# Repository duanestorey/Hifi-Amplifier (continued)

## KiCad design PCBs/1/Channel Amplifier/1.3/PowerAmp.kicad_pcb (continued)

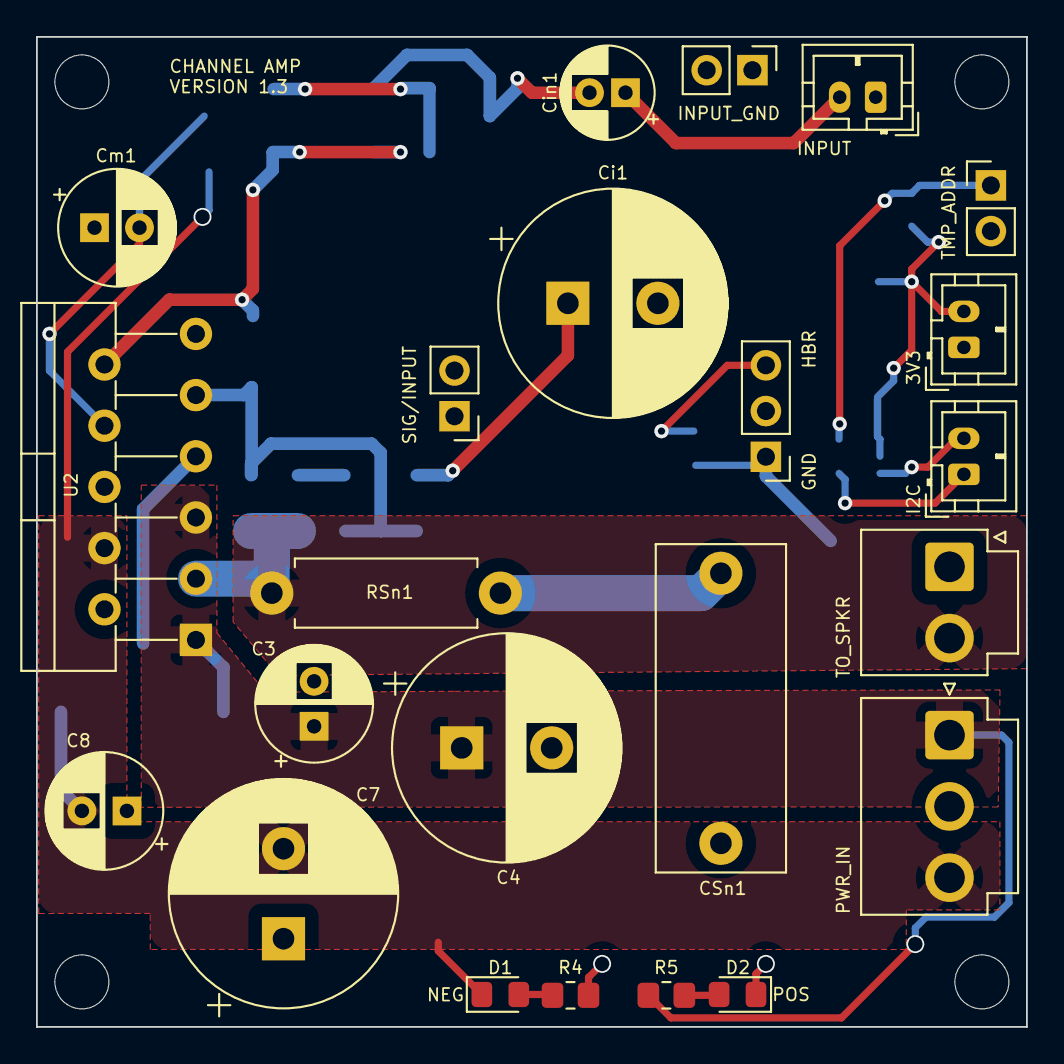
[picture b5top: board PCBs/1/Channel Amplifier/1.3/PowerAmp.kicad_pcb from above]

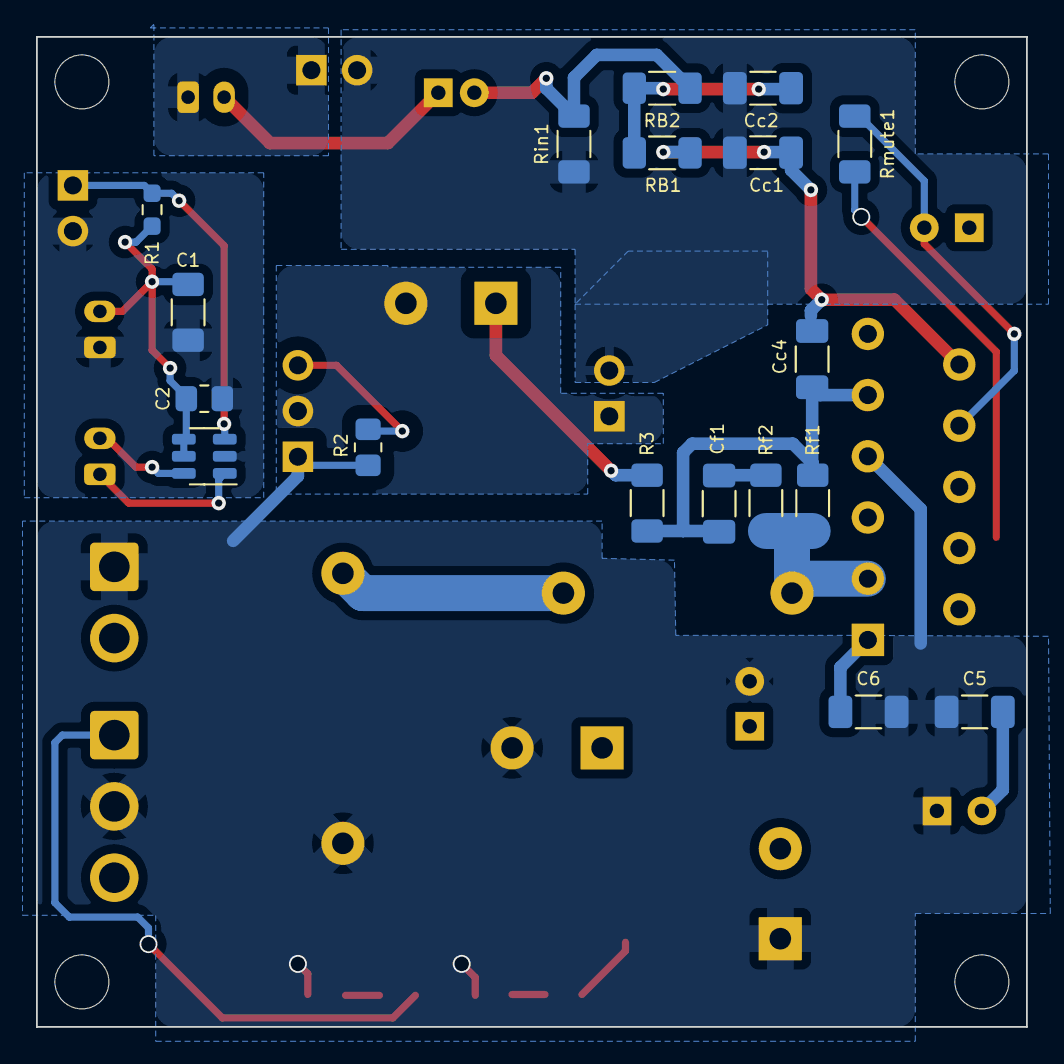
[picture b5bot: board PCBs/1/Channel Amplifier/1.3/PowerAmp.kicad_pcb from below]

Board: 2 copper layers, 55.0 x 55.0 mm, 45 parts (18 on the bottom side), 24 nets.

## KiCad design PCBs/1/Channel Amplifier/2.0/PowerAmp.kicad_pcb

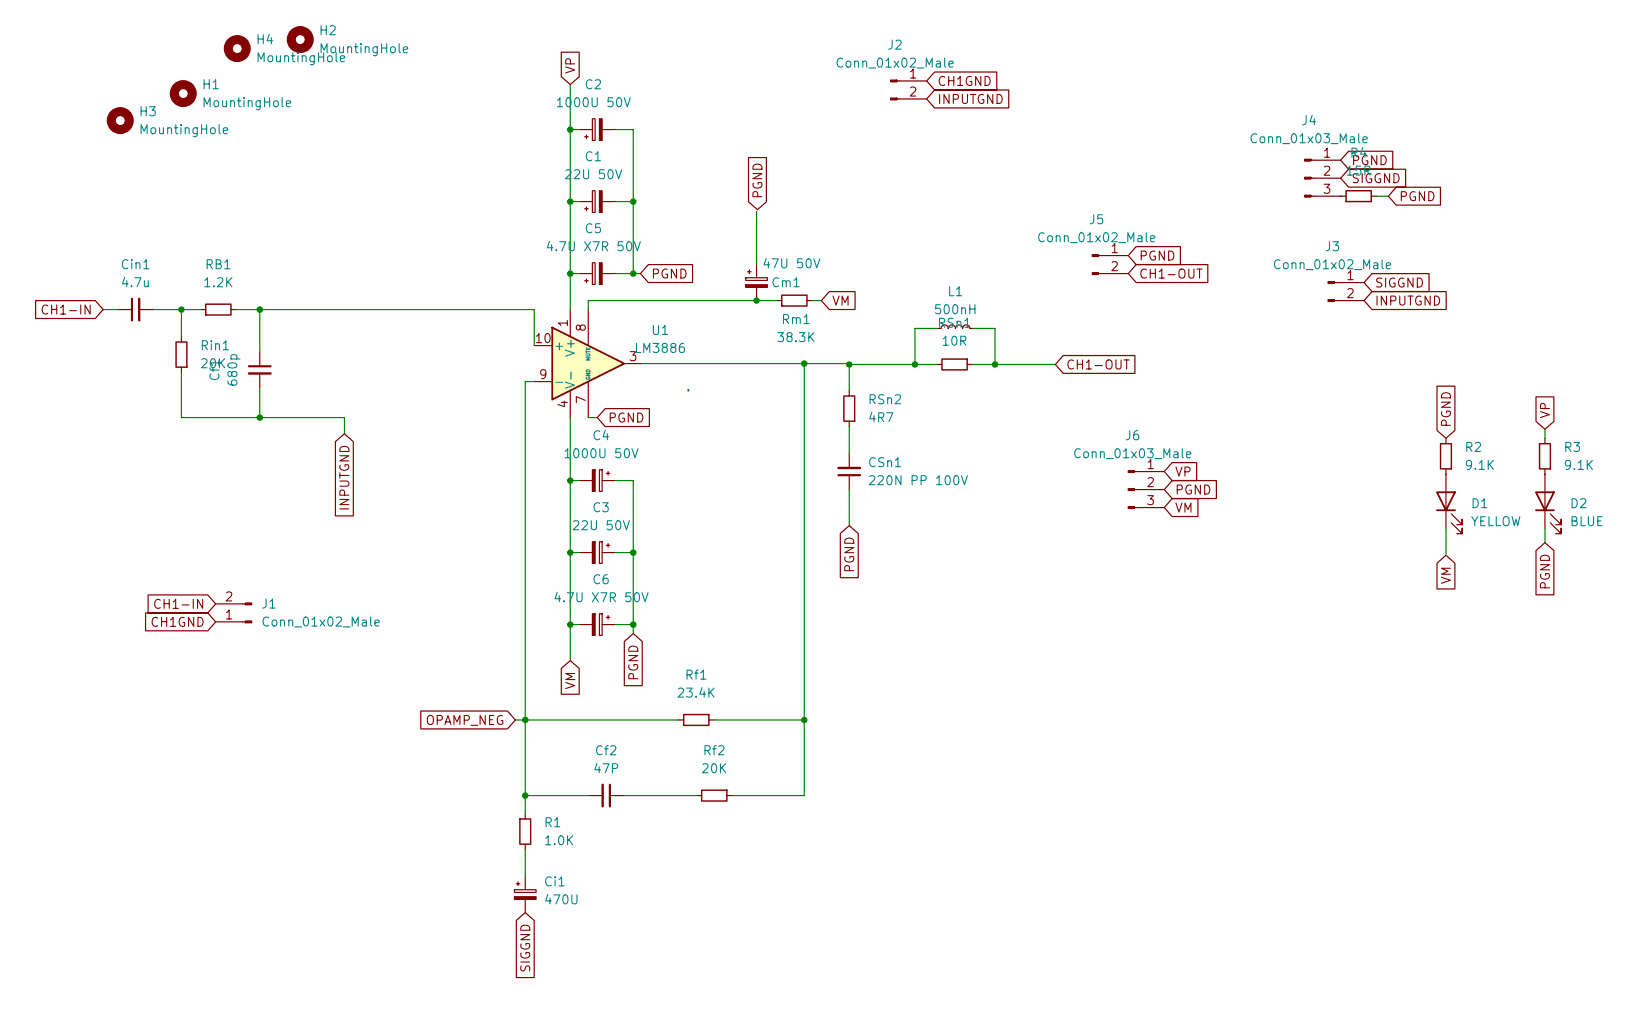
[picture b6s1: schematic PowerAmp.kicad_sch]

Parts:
C1, C3: 22U 50V; CP_Radial_D6.3mm_P2.50mm
C2, C4: 1000U 50V; CP_Radial_D12.5mm_P5.00mm
C5, C6: 4.7U X7R 50V; C_1206_3216Metric_Pad1.33x1.80mm_HandSolder
CSn1: 220N PP 100V; C_Rect_L18.0mm_W7.0mm_P15.00mm_FKS3_FKP3
Cf1: 680p; C_1206_3216Metric_Pad1.33x1.80mm_HandSolder
Cf2: 47P; C_1206_3216Metric_Pad1.33x1.80mm_HandSolder
Ci1: 470U; CP_Radial_D12.5mm_P5.00mm
Cin1: 4.7u; 4.7uF Polypropylene Aliexpress
Cm1: 47U 50V; CP_Radial_D6.3mm_P2.50mm
D1: YELLOW; LED_0805_2012Metric_Pad1.15x1.40mm_HandSolder
D2: BLUE; LED_0805_2012Metric_Pad1.15x1.40mm_HandSolder
H1, H2, H3, H4: MountingHole; MountingHole_3mm
J1: Conn_01x02_Male; JST_PH_B2B-PH-K_1x02_P2.00mm_Vertical
J2, J3: Conn_01x02_Male; PinHeader_1x02_P2.54mm_Vertical
J4: Conn_01x03_Male; PinHeader_1x03_P2.54mm_Vertical
J5: Conn_01x02_Male; JST_VH_B2P-VH_1x02_P3.96mm_Vertical
J6: Conn_01x03_Male; JST_VH_B3P-VH-B_1x03_P3.96mm_Vertical
L1: 500nH; 500nH Inductor Aliexpress Air Gap
R1: 1.0K; R_1206_3216Metric_Pad1.30x1.75mm_HandSolder
R2, R3: 9.1K; R_0805_2012Metric_Pad1.20x1.40mm_HandSolder
R4: 15R; R_0805_2012Metric_Pad1.20x1.40mm_HandSolder
RB1: 1.2K; R_1206_3216Metric_Pad1.30x1.75mm_HandSolder
RSn1: 10R; R_4020_10251Metric_Pad1.65x5.30mm_HandSolder
RSn2: 4R7; R_Axial_DIN0411_L9.9mm_D3.6mm_P12.70mm_Horizontal
Rf1: 23.4K; R_1206_3216Metric_Pad1.30x1.75mm_HandSolder
Rf2: 20K; R_1206_3216Metric_Pad1.30x1.75mm_HandSolder
Rin1: 20K; R_1206_3216Metric_Pad1.30x1.75mm_HandSolder
Rm1: 38.3K; R_1206_3216Metric_Pad1.30x1.75mm_HandSolder
U1: LM3886; TO-220-11_P3.4x5.08mm_StaggerOdd_Lead4.85mm_Vertical

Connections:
CH1-IN: Cin1.1, J1.2
CH1-OUT: J5.2, L1.2, RSn1.1
CH1GND: J1.1, J2.1
INPUTGND: Cf1.2, J2.2, J3.2, Rin1.1
unnamed: CSn1.2, RSn2.1
unnamed: Cf2.1, Rf2.2
unnamed: Ci1.1, R1.2
unnamed: Cin1.2, RB1.1, Rin1.2
unnamed: D1.2 (A), R2.1
unnamed: D2.2 (A), R3.1
unnamed: J4.3, R4.1
unnamed: L1.1, RSn1.2, RSn2.2, Rf1.1, Rf2.1, U1.3
unnamed: Cf1.1, RB1.2, U1.10 (+)
unnamed: Cm1.2, Rm1.1, U1.8 (MUTE)
OPAMP_NEG: Cf2.2, R1.1, Rf1.2, U1.9 (-)
PGND: C1.2, C2.2, C3.1, C4.1, C5.2, C6.1, CSn1.1, D2.1 (K), J4.1, J5.1, J6.2, R2.2, R4.2, U1.7 (GND)
SIGGND: Ci1.2, J3.1, J4.2
VM: C3.2, C4.2, C6.2, D1.1 (K), J6.3, Rm1.2, U1.4 (V-)
VP: C1.1, C2.1, C5.1, J6.1, R3.2, U1.1 (V+), U1.5 (V+)

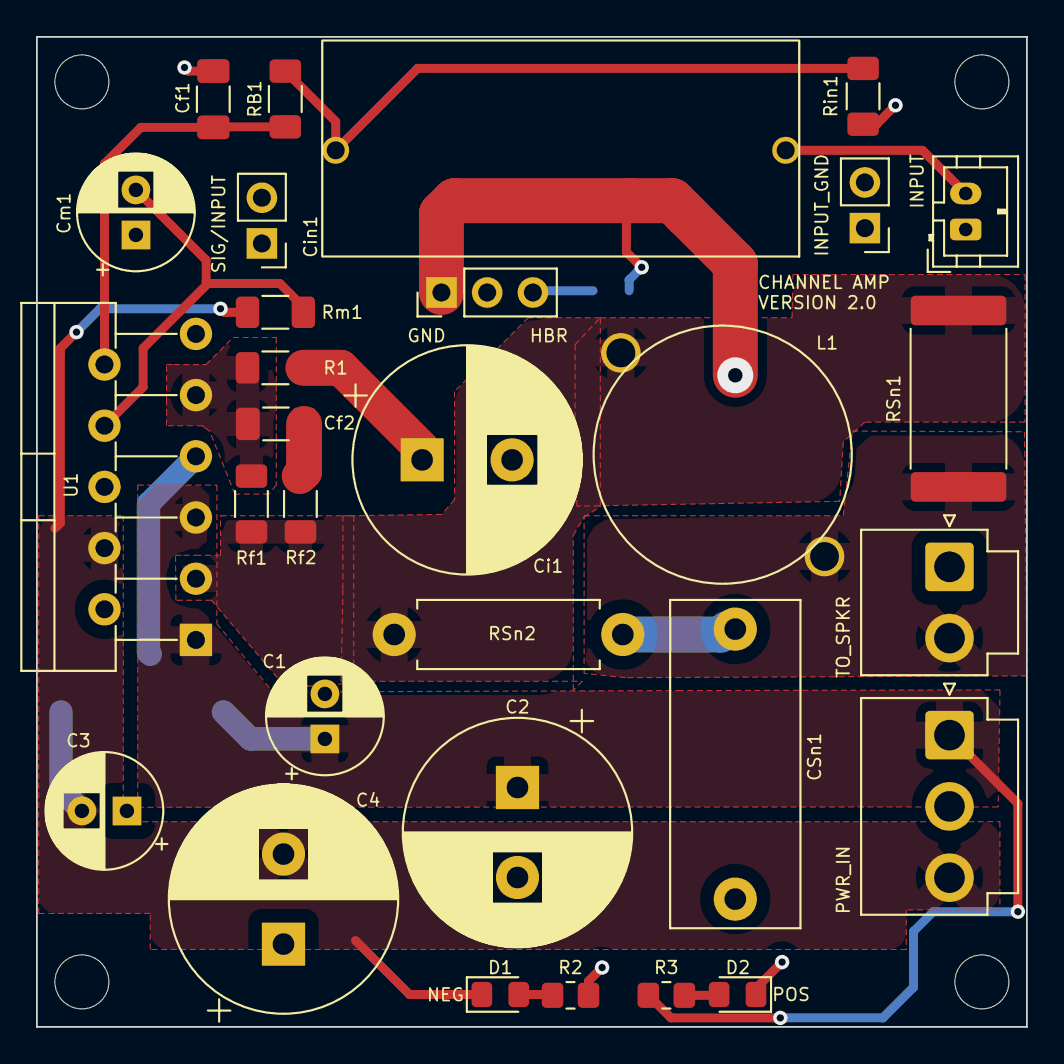
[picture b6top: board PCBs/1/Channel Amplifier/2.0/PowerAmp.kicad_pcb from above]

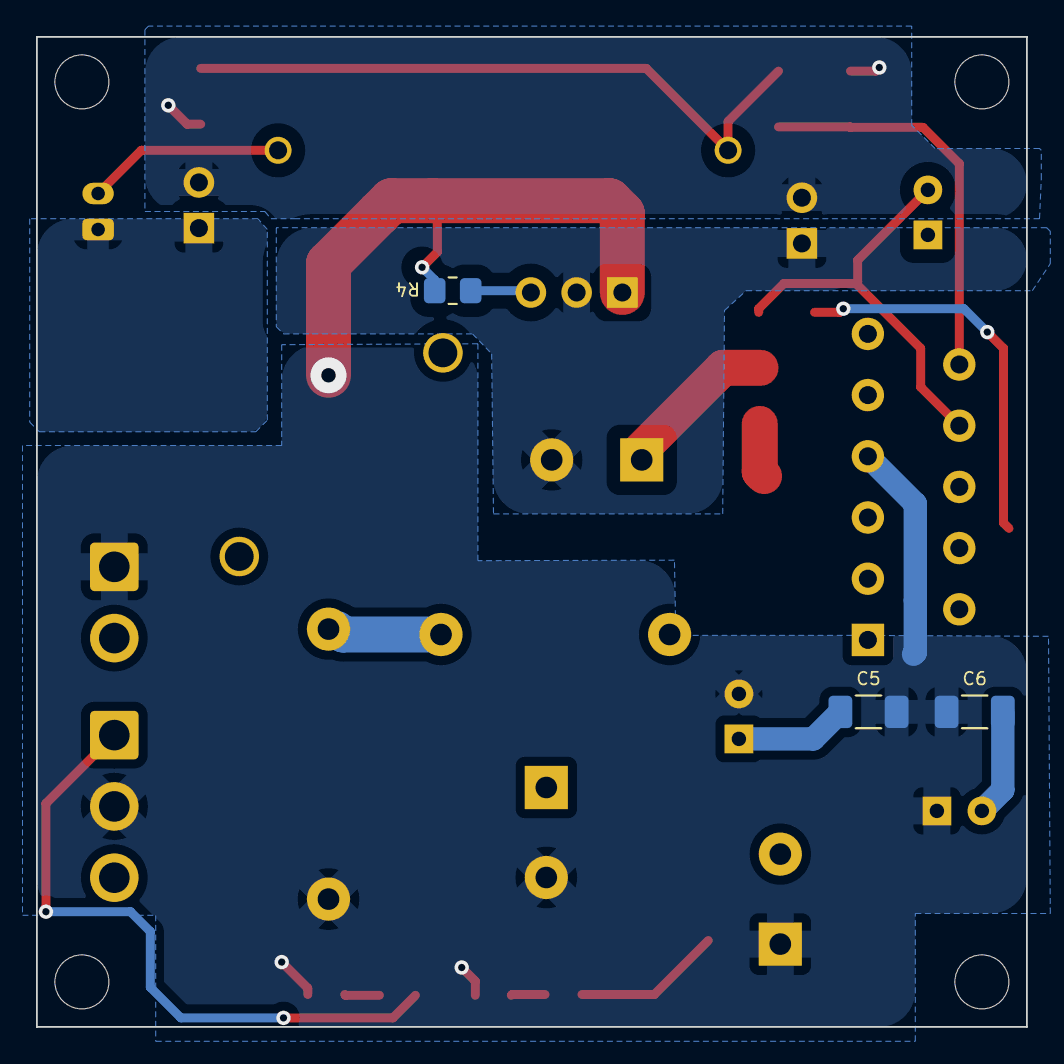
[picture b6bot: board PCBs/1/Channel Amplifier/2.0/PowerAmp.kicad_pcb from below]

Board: 2 copper layers, 55.0 x 55.0 mm, 37 parts (3 on the bottom side), 19 nets.
